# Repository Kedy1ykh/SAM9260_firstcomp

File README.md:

## SAM9260 My First computer build from scratch

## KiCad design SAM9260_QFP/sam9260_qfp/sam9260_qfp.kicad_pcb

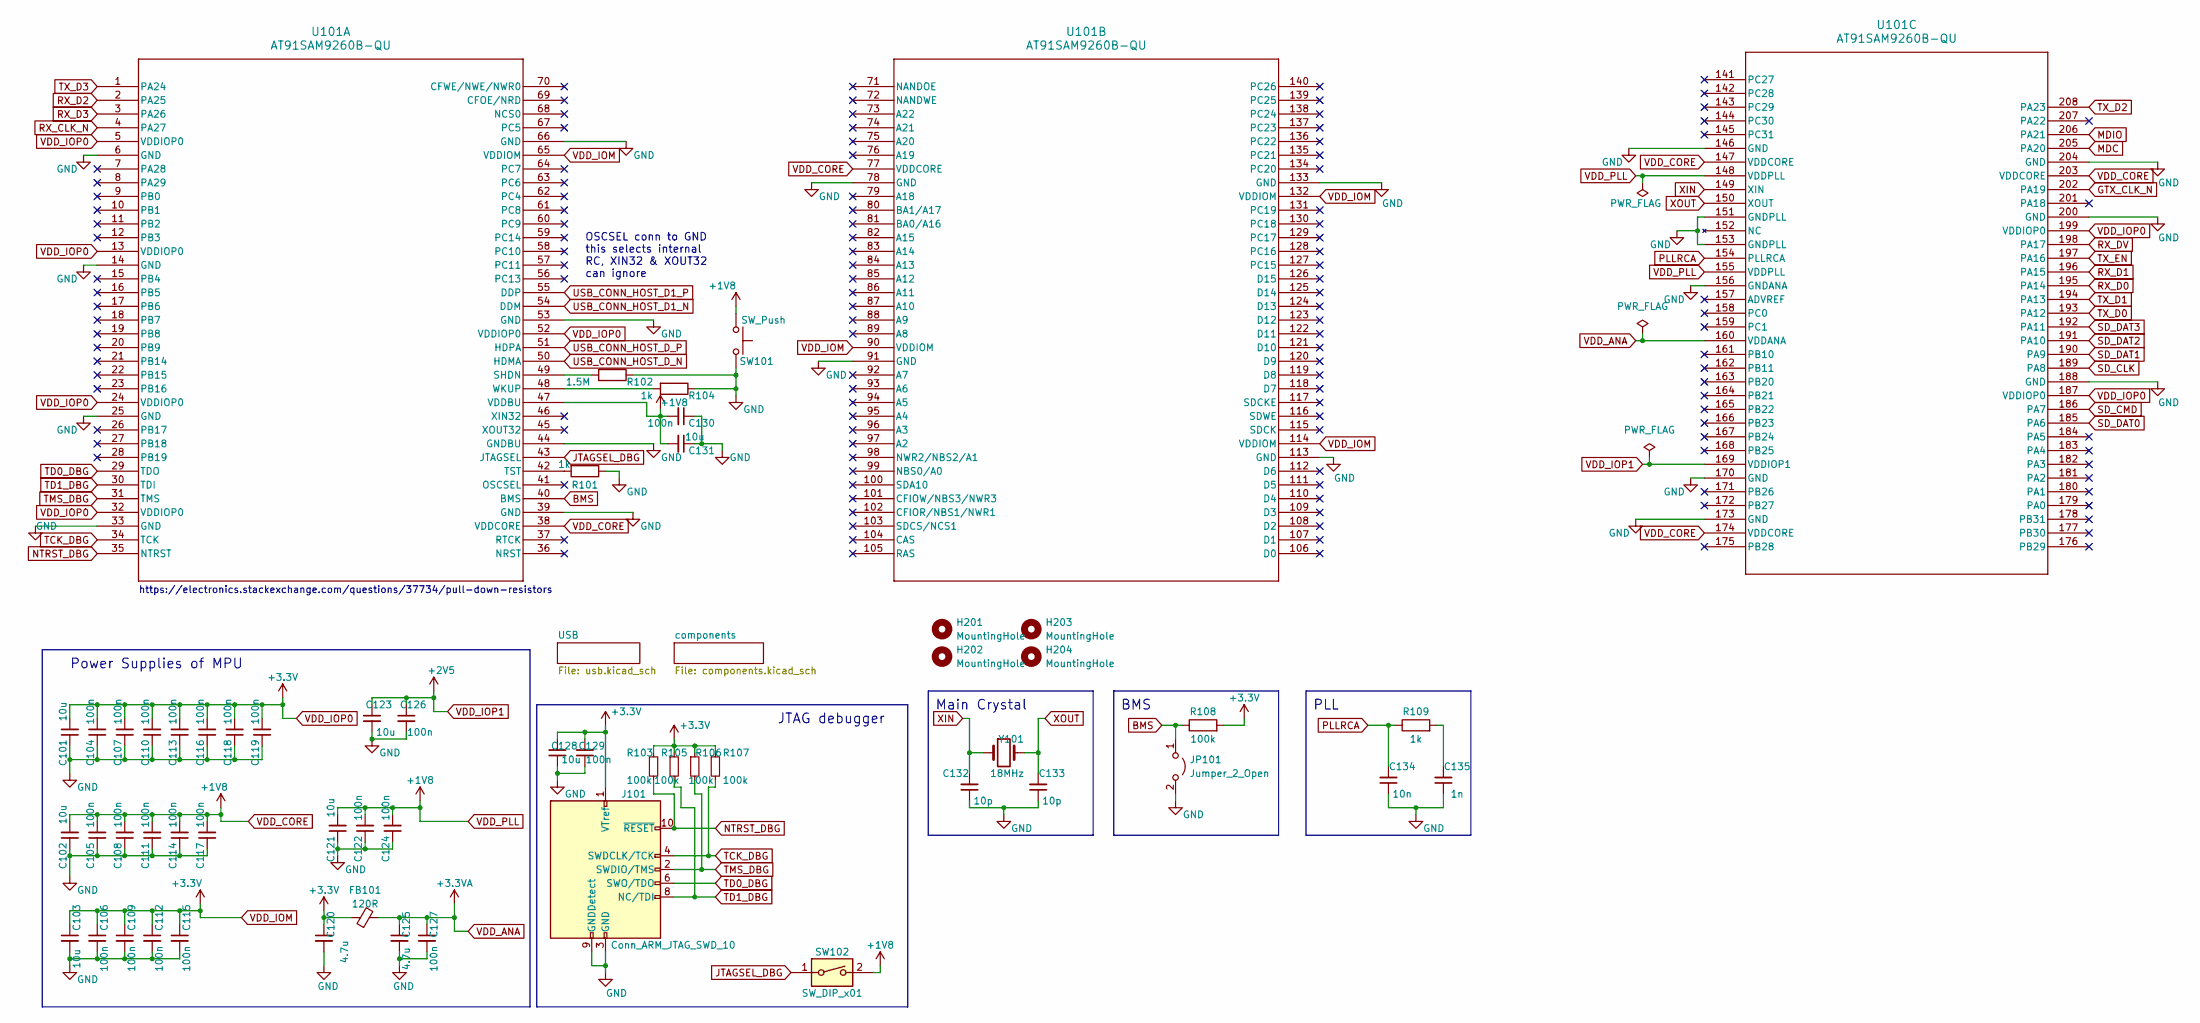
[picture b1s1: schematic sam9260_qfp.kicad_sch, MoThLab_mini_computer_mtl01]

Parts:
C101, C102, C103, C121, C123, C128, C131: 10u; C_0603_1608Metric
C104, C105, C106, C107, C108, C109, C110, C111, C112, C113, C114, C115, C116, C117, C118, C119, C122, C124, C126, C127, C129, C130: 100n; C_0402_1005Metric
C120, C125: 4.7u; C_0603_1608Metric
C132, C133: 10p; C_0402_1005Metric
C134: 10n; C_0402_1005Metric
C135: 1n; C_0402_1005Metric
FB101: 120R; L_0603_1608Metric
H201, H202, H203, H204: MountingHole; MountingHole_3mm
J101: Conn_ARM_JTAG_SWD_10; PinHeader_2x05_P1.00mm_Vertical_SMD
JP101: Jumper_2_Open; PinHeader_1x02_P1.00mm_Vertical
R101, R104, R109: 1k; R_0402_1005Metric
R102: 1.5M; R_0805_2012Metric
R103, R105, R106, R107, R108: 100k; R_0603_1608Metric
SW101: SW_Push; SW_Push_SPST_NO_Alps_SKRK
SW102: SW_DIP_x01; SW_DIP_SPSTx01_Slide_6.7x4.1mm_W6.73mm_P2.54mm_LowProfile_J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
U101: AT91SAM9260B-QU; PQFP208_ATM
Y101: 18MHz; Crystal_SMD_EuroQuartz_MQ2-2Pin_7.0x5.0mm

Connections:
AVDD33: C101.2, C103.1, C104.2, C106.1, C107.2, C109.1, C110.2, C112.1, C113.2, C115.1, C116.2, C118.2, C119.2, C120.1, C128.2, C129.2, FB101.1, J101.1 (VTref), R103.1, R105.1, R106.1, R107.1, R108.2, U101.5 (VDDIOP0), U101.13 (VDDIOP0), U101.24 (VDDIOP0), U101.32 (VDDIOP0), U101.52 (VDDIOP0), U101.65 (VDDIOM), U101.90 (VDDIOM), U101.114 (VDDIOM), U101.132 (VDDIOM), U101.187 (VDDIOP0), U101.199 (VDDIOP0); also elsewhere on the board
BMS: JP101.1 (A), R108.1, U101.40 (BMS)
GND: C101.1, C102.1, C103.2, C104.1, C105.1, C106.2, C107.1, C108.1, C109.2, C110.1, C111.1, C112.2, C113.1, C114.1, C115.2, C116.1, C117.1, C118.1, C119.1, C120.2, C121.1, C122.1, C123.2, C124.1, C125.2, C126.2, C127.2, C128.1, C129.1, C130.1, C131.1, C132.1, C133.1, C134.1, C135.1, J101.3 (GND), J101.5 (GND), J101.9 (GNDDetect), JP101.2 (B), R101.1, R102.1, R104.1, SW101.2, U101.6 (GND), U101.14 (GND), U101.25 (GND), U101.33 (GND), U101.39 (GND), U101.44 (GNDBU), U101.53 (GND), U101.66 (GND), U101.78 (GND), U101.91 (GND), U101.113 (GND), U101.133 (GND), U101.146 (GND), U101.151 (GNDPLL), U101.153 (GNDPLL), U101.156 (GNDANA), U101.170 (GND), U101.173 (GND), U101.188 (GND), U101.200 (GND), U101.204 (GND); also elsewhere on the board
GTX_CLK_N: U101.202 (PA19); also elsewhere on the board
JTAGSEL_DBG: SW102.1, U101.43 (JTAGSEL)
MDC: U101.205 (PA20); also elsewhere on the board
MDIO: U101.206 (PA21); also elsewhere on the board
NTRST_DBG: J101.10 (~RESET), R103.2, U101.35 (NTRST)
unnamed: C135.2, R109.2
unnamed: R102.2, U101.49 (SHDN)
unnamed: R101.2, U101.42 (TST)
unnamed: R104.2, U101.48 (WKUP)
PLLRCA: C134.2, R109.1, U101.154 (PLLRCA)
RX_CLK_N: U101.4 (PA27); also elsewhere on the board
RX_D0: U101.195 (PA14); also elsewhere on the board
RX_D1: U101.196 (PA15); also elsewhere on the board
RX_D2: U101.2 (PA25); also elsewhere on the board
RX_D3: U101.3 (PA26); also elsewhere on the board
RX_DV: U101.198 (PA17); also elsewhere on the board
SD_CLK: U101.189 (PA8); also elsewhere on the board
SD_CMD: U101.186 (PA7); also elsewhere on the board
SD_DAT0: U101.185 (PA6); also elsewhere on the board
SD_DAT1: U101.190 (PA9); also elsewhere on the board
SD_DAT2: U101.191 (PA10); also elsewhere on the board
SD_DAT3: U101.192 (PA11); also elsewhere on the board
TCK_DBG: J101.4 (SWDCLK/TCK), R107.2, U101.34 (TCK)
TD0_DBG: J101.6 (SWO/TDO), U101.29 (TDO)
TD1_DBG: J101.8 (NC/TDI), R105.2, U101.30 (TDI)
TMS_DBG: J101.2 (SWDIO/TMS), R106.2, U101.31 (TMS)
TX_D0: U101.193 (PA12); also elsewhere on the board
TX_D1: U101.194 (PA13); also elsewhere on the board
TX_D2: U101.208 (PA23); also elsewhere on the board
TX_D3: U101.1 (PA24); also elsewhere on the board
TX_EN: U101.197 (PA16); also elsewhere on the board
USB_CONN_HOST_D1_N: U101.54 (DDM); also elsewhere on the board
USB_CONN_HOST_D1_P: U101.55 (DDP); also elsewhere on the board
USB_CONN_HOST_D_N: U101.50 (HDMA); also elsewhere on the board
USB_CONN_HOST_D_P: U101.51 (HDPA); also elsewhere on the board
VDD_ANA: C125.1, C127.1, FB101.2, U101.160 (VDDANA)
VDD_CORE: C102.2, C105.2, C108.2, C111.2, C114.2, C117.2, C121.2, C122.2, C124.2, C130.2, C131.2, SW101.1, SW102.2, U101.38 (VDDCORE), U101.47 (VDDBU), U101.77 (VDDCORE), U101.147 (VDDCORE), U101.148 (VDDPLL), U101.155 (VDDPLL), U101.174 (VDDCORE), U101.203 (VDDCORE)
VDD_IOP1: C123.1, C126.1, U101.169 (VDDIOP1)
XIN: C132.2, U101.149 (XIN), Y101.1
XOUT: C133.2, U101.150 (XOUT), Y101.2

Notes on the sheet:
Power Supplies of MPU
https://electronics.stackexchange.com/questions/37734/pull-down-resistors
OSCSEL conn to GND this selects internal RC, XIN32 & XOUT32 can ignore
JTAG debugger
Main Crystal
PLL
BMS

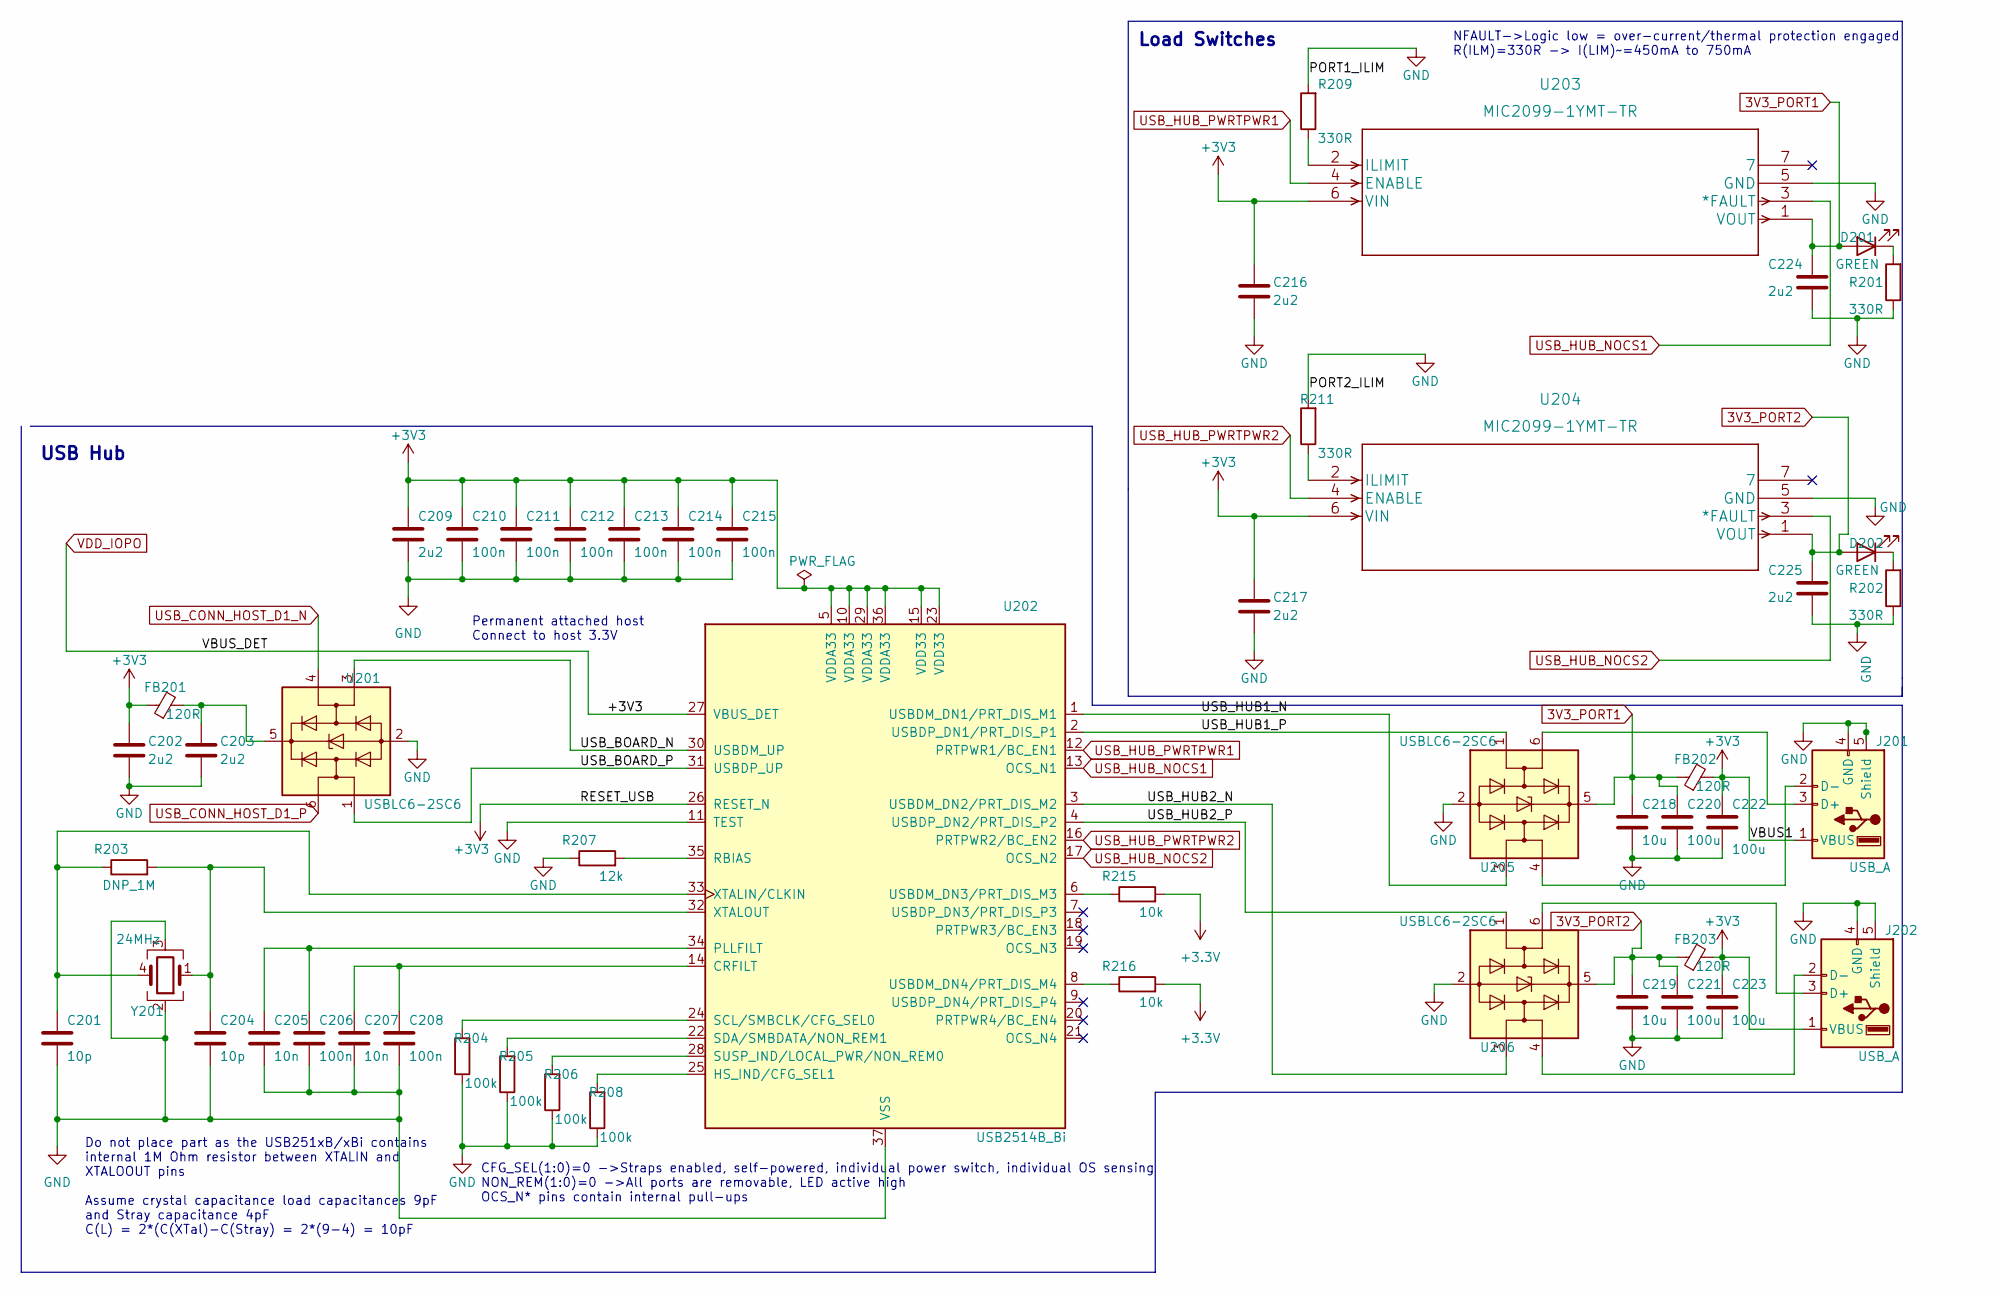
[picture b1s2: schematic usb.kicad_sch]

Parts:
C201, C204: 10p; C_0402_1005Metric
C202, C203, C209, C216, C217, C224, C225: 2u2; C_0603_1608Metric
C205, C207: 10n; C_0402_1005Metric
C206, C208, C210, C211, C212, C213, C214, C215: 100n; C_0402_1005Metric
C218, C219: 10u; C_0603_1608Metric
C220, C221, C222, C223: 100u; C_0402_1005Metric
D201, D202: GREEN; LED_0603_1608Metric
FB201, FB202, FB203: 120R; L_0603_1608Metric
J201, J202: USB_A; USB_A_Molex_67643_Horizontal
R201, R202, R209, R211: 330R; R_0402_1005Metric
R203: DNP_1M; R_0805_2012Metric
R204, R205, R206, R208: 100k; R_0603_1608Metric
R207: 12k; R_0603_1608Metric
R215, R216: 10k; R_0603_1608Metric
U201, U205, U206: USBLC6-2SC6; SOT-23-6
U202: USB2514B_Bi; QFN-36-1EP_6x6mm_P0.5mm_EP3.7x3.7mm
U203, U204: MIC2099-1YMT-TR; TMLF-6_MT_MCH
Y201: 24MHz; Crystal_SMD_EuroQuartz_MQ-4Pin_7.0x5.0mm

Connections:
3V3_PORT1: C218.1, C220.1, C224.1, D201.2 (A), FB202.1, U203.1 (VOUT), U205.5 (VBUS)
3V3_PORT2: C219.1, C221.1, C225.1, D202.2 (A), FB203.1, U204.1 (VOUT), U206.5 (VBUS)
/USB/USB_BOARD_N: U201.3 (I/O2), U202.30 (USBDM_UP)
/USB/USB_BOARD_P: U201.1 (I/O1), U202.31 (USBDP_UP)
/USB/USB_HUB1_N: U202.1 (USBDM_DN1/PRT_DIS_M1), U205.3 (I/O2)
/USB/USB_HUB1_P: U202.2 (USBDP_DN1/PRT_DIS_P1), U205.1 (I/O1)
/USB/USB_HUB2_N: U202.3 (USBDM_DN2/PRT_DIS_M2), U206.3 (I/O2)
/USB/USB_HUB2_P: U202.4 (USBDP_DN2/PRT_DIS_P2), U206.1 (I/O1)
AVDD33: R215.2, R216.2; also elsewhere on the board
GND: C201.2, C202.2, C203.2, C204.2, C205.2, C206.2, C207.2, C208.2, C209.2, C210.2, C211.2, C212.2, C213.2, C214.2, C215.2, C216.2, C217.2, C218.2, C219.2, C220.2, C221.2, C222.2, C223.2, C224.2, C225.2, J201.4 (GND), J201.5 (Shield), J202.4 (GND), J202.5 (Shield), R201.1, R202.1, R204.1, R205.1, R206.1, R207.1, R208.1, R209.2, R211.2, U201.2 (GND), U202.11 (TEST), U202.37 (VSS), U203.5 (GND), U204.5 (GND), U205.2 (GND), U206.2 (GND), Y201.2, Y201.3; also elsewhere on the board
unnamed: D201.1 (K), R201.2
unnamed: D202.1 (K), R202.2
unnamed: J201.3 (D+), U205.6 (I/O1)
unnamed: J201.2 (D-), U205.4 (I/O2)
unnamed: J202.3 (D+), U206.6 (I/O1)
unnamed: J202.2 (D-), U206.4 (I/O2)
unnamed: C203.1, FB201.2, U201.5 (VBUS)
unnamed: C207.1, C208.1, U202.14 (CRFILT)
unnamed: R208.2, U202.25 (HS_IND/CFG_SEL1)
unnamed: C205.1, C206.1, U202.34 (PLLFILT)
unnamed: R207.2, U202.35 (RBIAS)
unnamed: R204.2, U202.24 (SCL/SMBCLK/CFG_SEL0)
unnamed: R205.2, U202.22 (SDA/SMBDATA/NON_REM1)
unnamed: R206.2, U202.28 (SUSP_IND/LOCAL_PWR/NON_REM0)
unnamed: R215.1, U202.6 (USBDM_DN3/PRT_DIS_M3)
unnamed: R216.1, U202.8 (USBDM_DN4/PRT_DIS_M4)
unnamed: C201.1, R203.1, U202.33 (XTALIN/CLKIN), Y201.4
unnamed: C204.1, R203.2, U202.32 (XTALOUT), Y201.1
unnamed: R209.1, U203.2 (ILIMIT)
unnamed: R211.1, U204.2 (ILIMIT)
USB_CONN_HOST_D1_N: U201.4 (I/O2); also elsewhere on the board
USB_CONN_HOST_D1_P: U201.6 (I/O1); also elsewhere on the board
USB_HUB_NOCS1: U202.13 (OCS_N1), U203.3 (*FAULT)
USB_HUB_NOCS2: U202.17 (OCS_N2), U204.3 (*FAULT)
USB_HUB_PWRTPWR1: U202.12 (PRTPWR1/BC_EN1), U203.4 (ENABLE)
USB_HUB_PWRTPWR2: U202.16 (PRTPWR2/BC_EN2), U204.4 (ENABLE)
VDD_IOPO: C202.1, C209.1, C210.1, C211.1, C212.1, C213.1, C214.1, C215.1, C216.1, C217.1, C222.1, C223.1, FB201.1, FB202.2, FB203.2, J201.1 (VBUS), J202.1 (VBUS), U202.5 (VDDA33), U202.10 (VDDA33), U202.15 (VDD33), U202.23 (VDD33), U202.26 (RESET_N), U202.27 (VBUS_DET), U202.29 (VDDA33), U202.36 (VDDA33), U203.6 (VIN), U204.6 (VIN)

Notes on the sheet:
Do not place part as the USB251xB/xBi contains internal 1M Ohm resistor between XTALIN and XTALOOUT pins Assume crystal capacitance load capacitances 9pF and Stray capacitance 4pF C(L) = 2*(C(XTal)-C(Stray) = 2*(9-4) = 10pF
NFAULT->Logic low = over-current/thermal protection engaged R(ILM)=330R -> I(LIM)~=450mA to 750mA
USB Hub
Load Switches
CFG_SEL(1:0)=0 ->Straps enabled, self-powered, individual power switch, individual OS sensing NON_REM(1:0)=0 ->All ports are removable, LED active high OCS_N* pins contain internal pull-ups
Permanent attached host Connect to host 3.3V

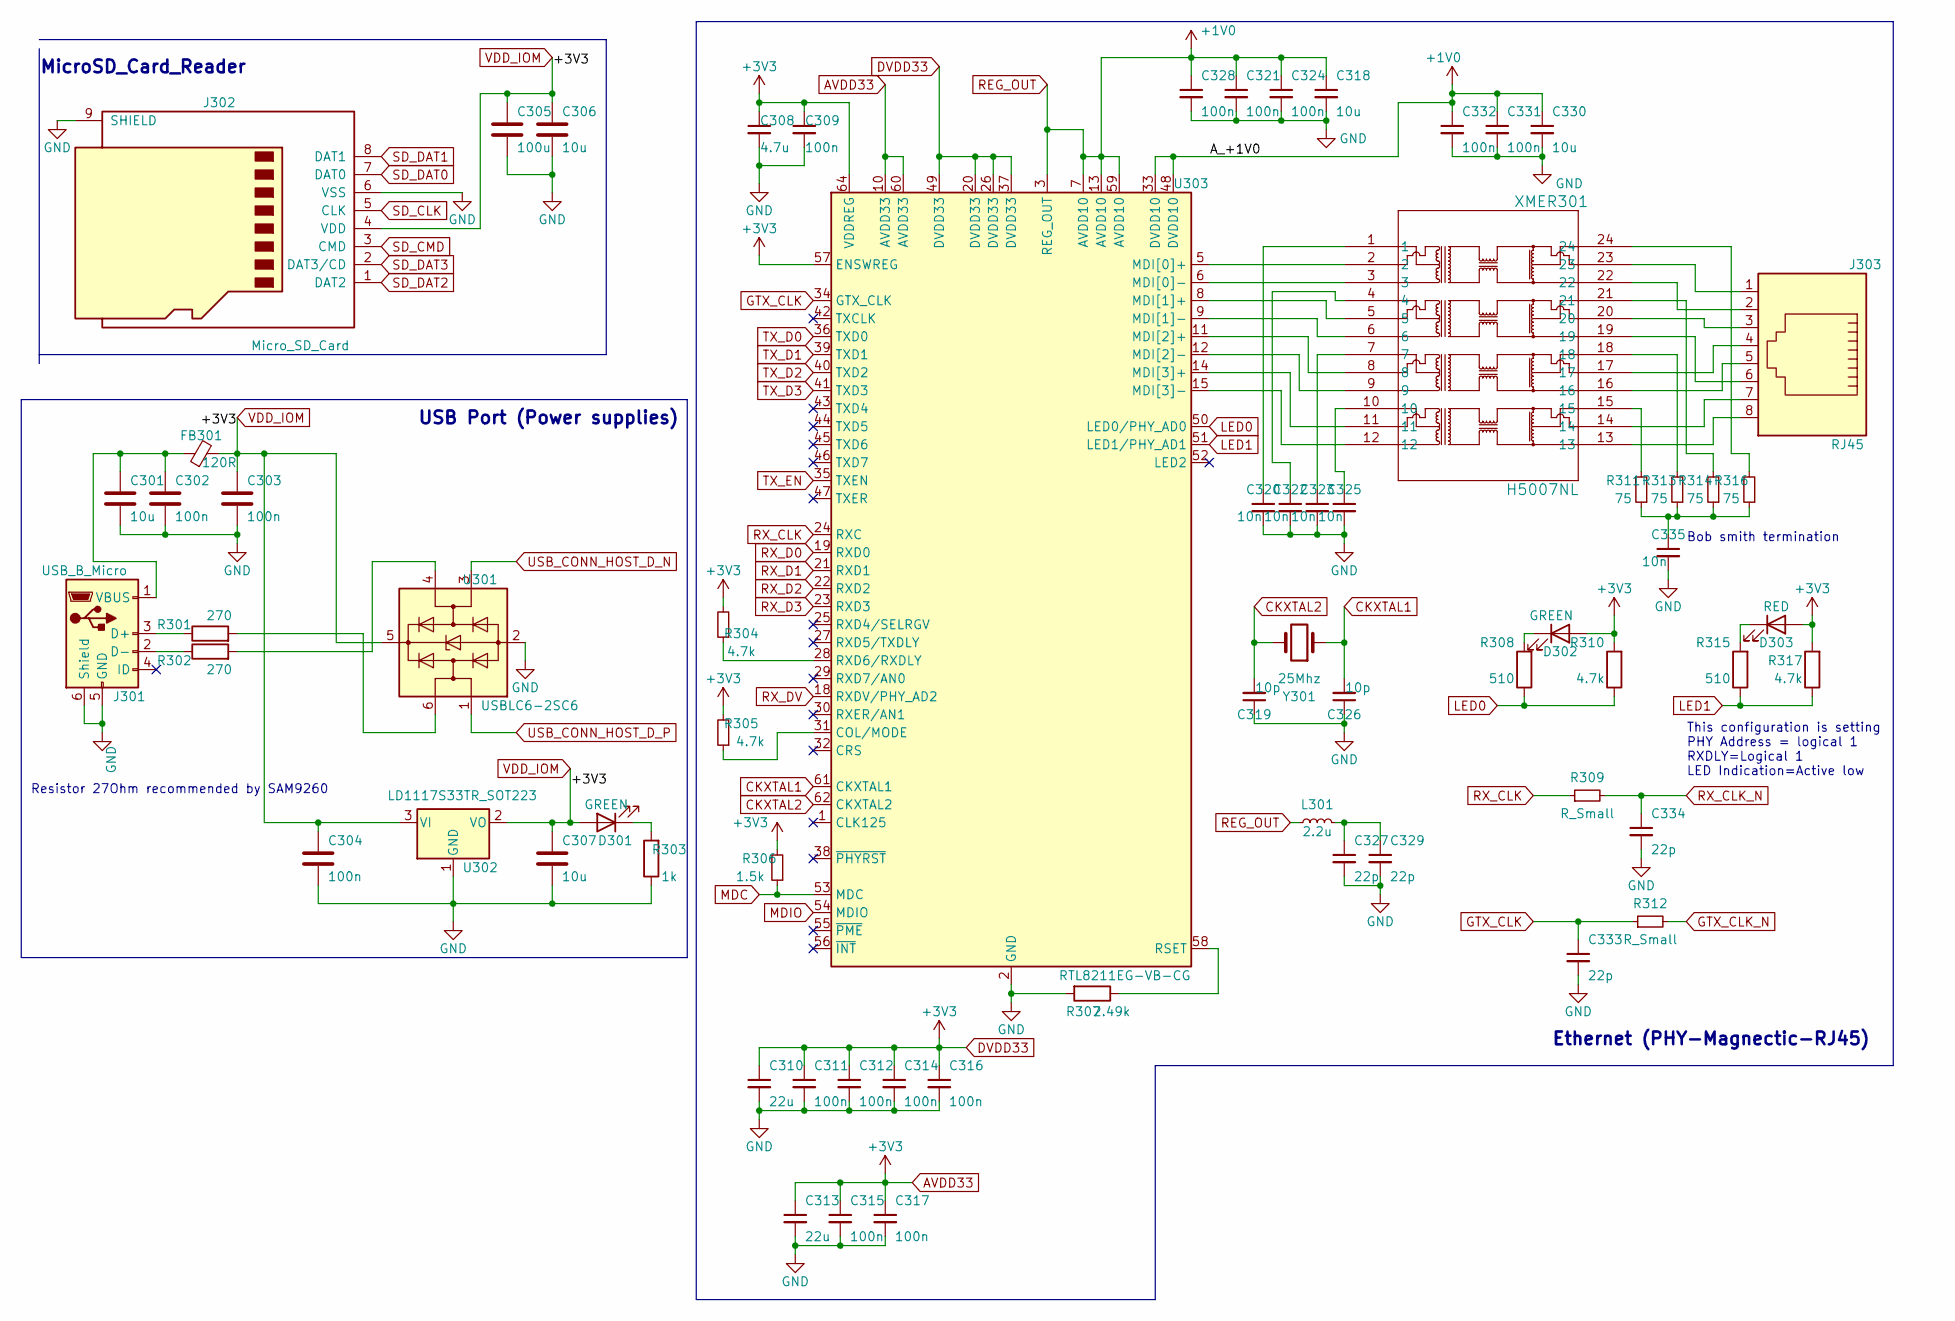
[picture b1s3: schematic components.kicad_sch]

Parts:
C301, C306, C307, C318, C330: 10u; C_0603_1608Metric
C302, C303, C304, C309, C311, C312, C314, C315, C316, C317, C321, C324, C328, C331, C332: 100n; C_0402_1005Metric
C305: 100u; C_0402_1005Metric
C308: 4.7u; C_0603_1608Metric
C310, C313: 22u; C_0603_1608Metric
C319, C326: 10p; C_0402_1005Metric
C320, C322, C323, C325, C335: 10n; C_0402_1005Metric
C327, C329, C333, C334: 22p; C_0402_1005Metric
D301, D302: GREEN; LED_0603_1608Metric
D303: RED; LED_0603_1608Metric
FB301: 120R; L_0603_1608Metric
J301: USB_B_Micro; USB_Micro-B_Molex-105017-0001
J302: Micro_SD_Card; microSD_HC_Molex_47219-2001
J303: RJ45; RJ45_Wuerth_7499010001A_Horizontal
L301: 2.2u; L_0603_1608Metric
R301, R302: 270; R_0402_1005Metric
R303: 1k; R_0402_1005Metric
R304, R305, R310, R317: 4.7k; R_0402_1005Metric
R306: 1.5k; R_0402_1005Metric
R307: 2.49k; R_0402_1005Metric
R308, R315: 510; R_0402_1005Metric
R309, R312: R_Small; R_0402_1005Metric
R311, R313, R314, R316: 75; R_0201_0603Metric
U301: USBLC6-2SC6; SOT-23-6
U302: LD1117S33TR_SOT223; SOT-223-3_TabPin2
U303: RTL8211EG-VB-CG; QFN-64-1EP_9x9mm_P0.5mm_EP3.8x3.8mm
XMER301: H5007NL; H5007NL_PUL
Y301: 25Mhz; Crystal_SMD_EuroQuartz_MQ2-2Pin_7.0x5.0mm

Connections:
AVDD33: C303.1, C304.1, C305.1, C306.1, C307.1, C308.1, C309.1, C310.1, C311.1, C312.1, C313.1, C314.1, C315.1, C316.1, C317.1, D301.2 (A), D302.2 (A), D303.2 (A), FB301.2, J302.4 (VDD), R304.2, R305.2, R306.2, R310.2, R317.2, U301.5 (VBUS), U302.2 (VO), U302.3 (VI), U303.10 (AVDD33), U303.20 (DVDD33), U303.26 (DVDD33), U303.37 (DVDD33), U303.49 (DVDD33), U303.57 (ENSWREG), U303.60 (AVDD33), U303.64 (VDDREG); also elsewhere on the board
CKXTAL1: C326.2, U303.61 (CKXTAL1), Y301.1
CKXTAL2: C319.2, U303.62 (CKXTAL2), Y301.2
GND: C301.2, C302.2, C303.2, C304.2, C305.2, C306.2, C307.2, C308.2, C309.2, C310.2, C311.2, C312.2, C313.2, C314.2, C315.2, C316.2, C317.2, C318.2, C319.1, C320.2, C321.2, C322.2, C323.2, C324.2, C325.2, C326.1, C327.2, C328.2, C329.2, C330.2, C331.2, C332.2, C333.2, C334.2, C335.2, J301.5 (GND), J301.6 (Shield), J302.6 (VSS), J302.9 (SHIELD), R303.1, R307.2, U301.2 (GND), U302.1 (GND), U303.2 (GND), U303.4 (GND), U303.63 (GND), U303.65 (GND); also elsewhere on the board
GTX_CLK: C333.1, R312.1, U303.34 (GTX_CLK)
GTX_CLK_N: R312.2; also elsewhere on the board
LED0: R308.1, R310.1, U303.50 (LED0/PHY_AD0)
LED1: R315.1, R317.1, U303.51 (LED1/PHY_AD1)
MDC: R306.1, U303.53 (MDC); also elsewhere on the board
MDIO: U303.54 (MDIO); also elsewhere on the board
unnamed: C320.1, XMER301.1
unnamed: C322.1, XMER301.4
unnamed: C323.1, XMER301.7
unnamed: C325.1, XMER301.10
unnamed: C327.1, C329.1, L301.2
unnamed: C335.1, R311.1, R313.1, R314.1, R316.1
unnamed: D301.1 (K), R303.2
unnamed: D302.1 (K), R308.2
unnamed: D303.1 (K), R315.2
unnamed: J301.3 (D+), R301.1
unnamed: J301.2 (D-), R302.1
unnamed: C301.1, C302.1, FB301.1, J301.1 (VBUS)
unnamed: J303.1, XMER301.23
unnamed: J303.2, XMER301.22
unnamed: J303.3, XMER301.20
unnamed: J303.4, XMER301.17
unnamed: J303.5, XMER301.16
unnamed: J303.6, XMER301.19
unnamed: J303.7, XMER301.14
unnamed: J303.8, XMER301.13
unnamed: R301.2, U301.6 (I/O1)
unnamed: R302.2, U301.4 (I/O2)
unnamed: R311.2, XMER301.15
unnamed: R313.2, XMER301.18
unnamed: R314.2, XMER301.21
unnamed: R316.2, XMER301.24
unnamed: R305.1, U303.31 (COL/MODE)
unnamed: U303.5 (MDI[0]+), XMER301.2
unnamed: U303.6 (MDI[0]-), XMER301.3
unnamed: U303.8 (MDI[1]+), XMER301.5
unnamed: U303.9 (MDI[1]-), XMER301.6
unnamed: U303.11 (MDI[2]+), XMER301.8
unnamed: U303.12 (MDI[2]-), XMER301.9
unnamed: U303.14 (MDI[3]+), XMER301.11
unnamed: U303.15 (MDI[3]-), XMER301.12
unnamed: R307.1, U303.58 (RSET)
unnamed: R304.1, U303.28 (RXD6/RXDLY)
REG_OUT: C318.1, C321.1, C324.1, C328.1, C330.1, C331.1, C332.1, L301.1, U303.3 (REG_OUT), U303.7 (AVDD10), U303.13 (AVDD10), U303.33 (DVDD10), U303.48 (DVDD10), U303.59 (AVDD10)
RX_CLK: R309.1, U303.24 (RXC)
RX_CLK_N: C334.1, R309.2; also elsewhere on the board
RX_D0: U303.19 (RXD0); also elsewhere on the board
RX_D1: U303.21 (RXD1); also elsewhere on the board
RX_D2: U303.22 (RXD2); also elsewhere on the board
RX_D3: U303.23 (RXD3); also elsewhere on the board
RX_DV: U303.18 (RXDV/PHY_AD2); also elsewhere on the board
SD_CLK: J302.5 (CLK); also elsewhere on the board
SD_CMD: J302.3 (CMD); also elsewhere on the board
SD_DAT0: J302.7 (DAT0); also elsewhere on the board
SD_DAT1: J302.8 (DAT1); also elsewhere on the board
SD_DAT2: J302.1 (DAT2); also elsewhere on the board
SD_DAT3: J302.2 (DAT3/CD); also elsewhere on the board
TX_D0: U303.36 (TXD0); also elsewhere on the board
TX_D1: U303.39 (TXD1); also elsewhere on the board
TX_D2: U303.40 (TXD2); also elsewhere on the board
TX_D3: U303.41 (TXD3); also elsewhere on the board
TX_EN: U303.35 (TXEN); also elsewhere on the board
USB_CONN_HOST_D_N: U301.3 (I/O2); also elsewhere on the board
USB_CONN_HOST_D_P: U301.1 (I/O1); also elsewhere on the board

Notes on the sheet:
USB Port (Power supplies)
Ethernet (PHY-Magnectic-RJ45)
Resistor 27Ohm recommended by SAM9260
MicroSD_Card_Reader
This configuration is setting PHY Address = logical 1 RXDLY=Logical 1 LED Indication=Active low
Bob smith termination

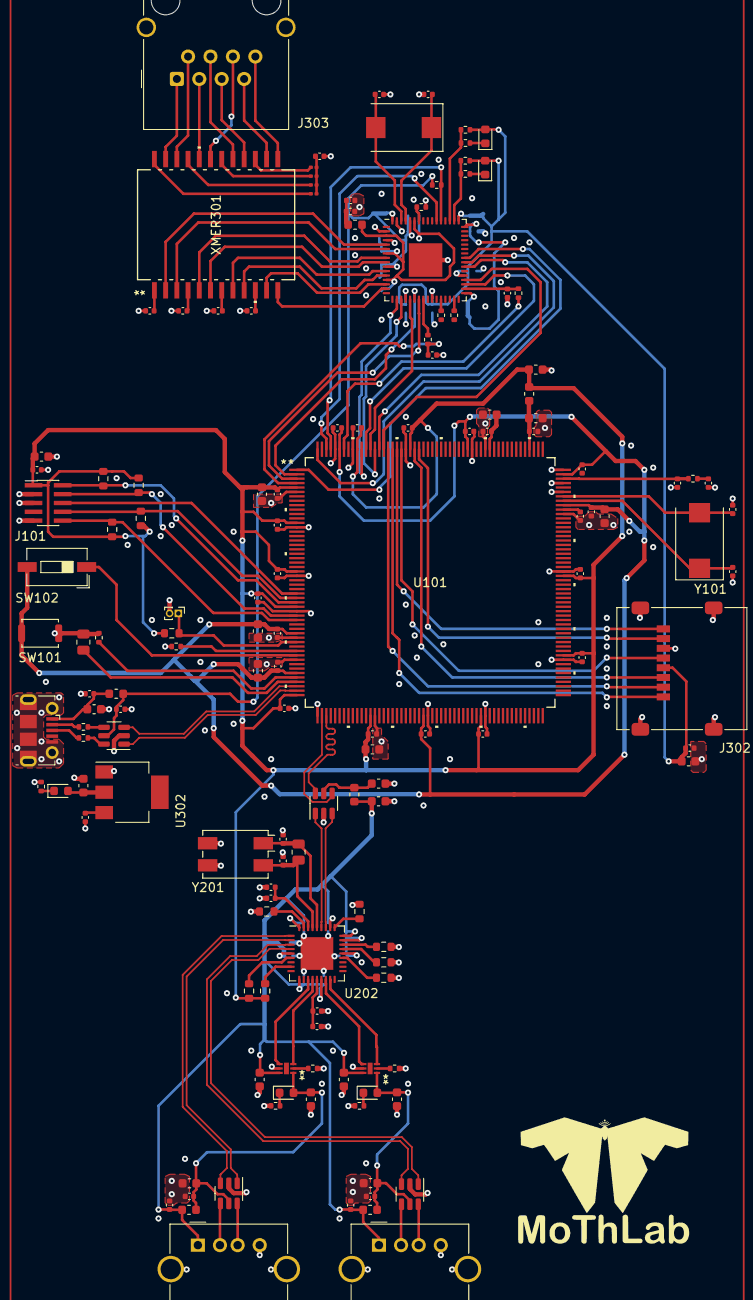
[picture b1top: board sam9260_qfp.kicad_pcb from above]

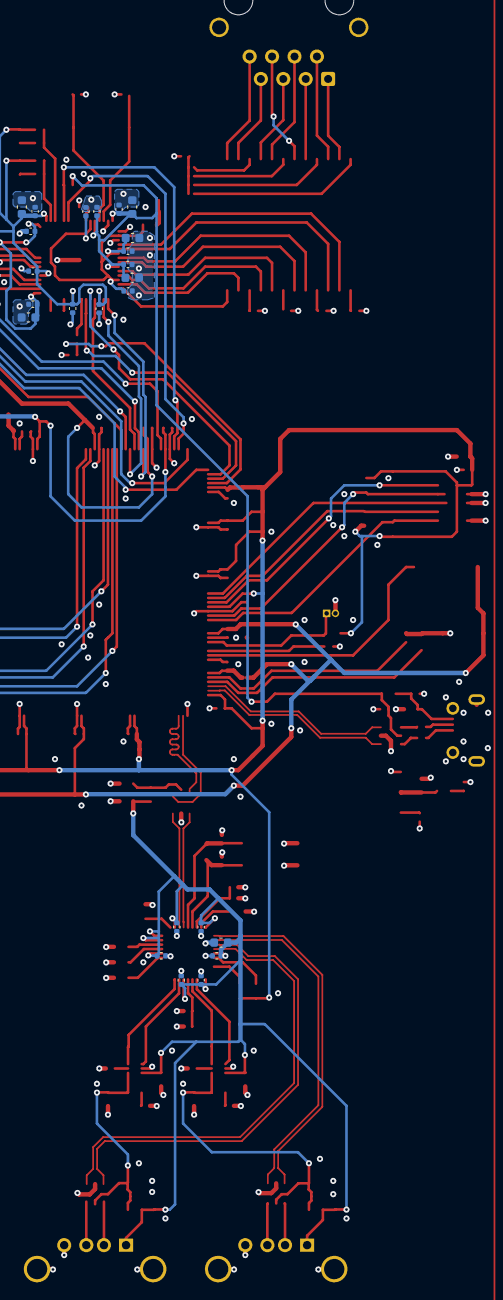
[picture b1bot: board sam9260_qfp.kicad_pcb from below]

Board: 4 copper layers, 171 parts (24 on the bottom side), 120 nets.

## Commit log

2023-05-30 First commit with completed schematic
2023-06-10 Completed component placing
2023-08-12 updated layout
2023-08-30 Completed routing, need to add logo
2023-11-30 Added logo
